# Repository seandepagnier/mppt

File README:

MPPT charge controller for maximum power

- free software and hardware design.  Can be adapted to other requirements.
- all ceramic capacitors.
- buck/boost design allow either higher or lower voltage of battery vs panel.
- components rated for up to 48 volt system (60 volt mosfets)
- voltage and current monitoring on both input and output.
- high-efficiency regulators to power the 3.3v logic as well as the 10v needed for gate drive.

This project uses the stm32duino environment.

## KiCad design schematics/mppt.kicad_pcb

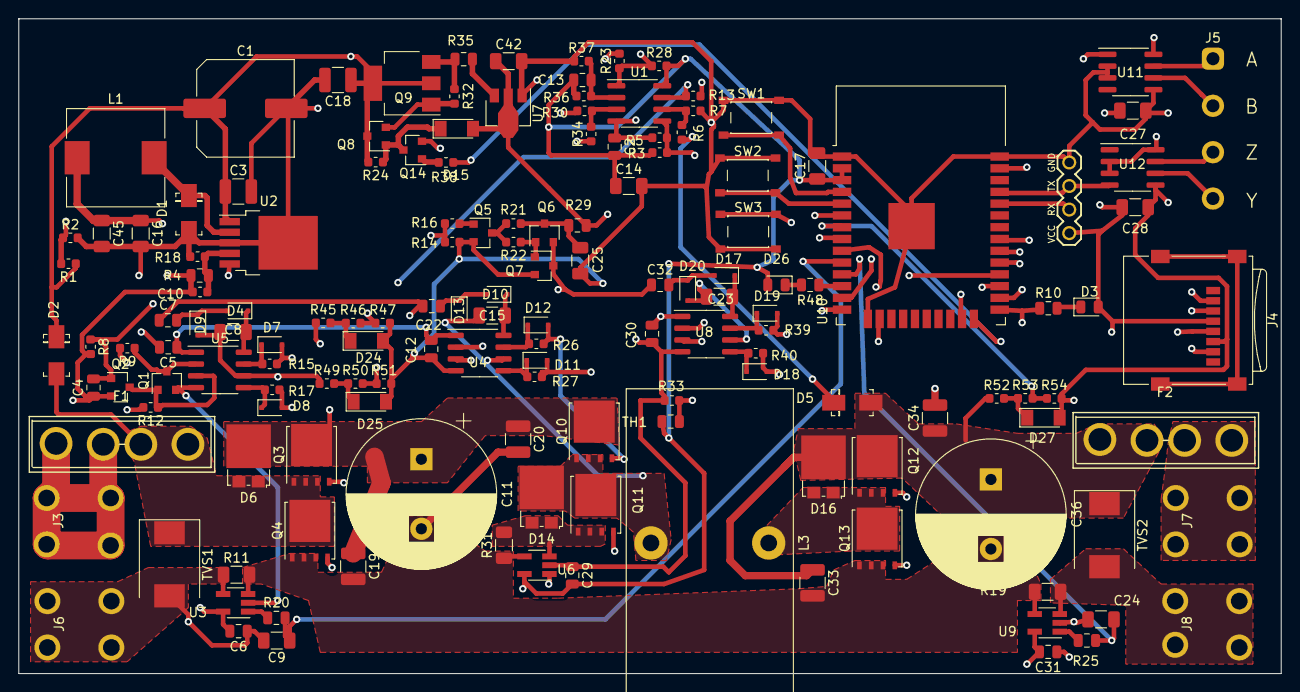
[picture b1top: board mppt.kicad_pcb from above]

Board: 4 copper layers, 136.1 x 70.6 mm, 152 parts (0 on the bottom side), 89 nets.

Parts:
C1: 33uF 100v; C_Elec_10x10.2
C2, C6, C7, C13, C22, C32: 100nF; C_0805_2012Metric
C3, C18: 4.7uF; C_1210_3225Metric
C4, C5, C12, C30: 10uF; C_0805_2012Metric
C8, C9, C15, C23, C24, C27, C28, C42: 1uF; C_1206_3216Metric
C10: 33nF; C_0603_1608Metric
C11, C36: 470uF; CP_Radial_D16.0mm_P7.50mm
C14, C16, C17, C25, C45: 10uF; C_1206_3216Metric
C19, C20, C33, C34: 4.7uF 100v; C_1210_3225Metric
C29, C31: 1uF; C_0805_2012Metric
D1, D2, D5: D; DO-214AC
D3: GREEN; LED_0805_2012Metric
D4, D7, D8, D9, D10, D11, D12, D13, D17, D18, D19, D20: D; D_SOD-323F
D6, D14, D16: D_Schottky_AAK; TO-277A
D15, D24, D25, D27: 5.6v; D_MiniMELF
D26: YELLOW; LED_0805_2012Metric
F1, F2: FUSE; BladeFuse-CarType
J2: UART; uart
J3: IN+; screw_terminal
J4: Micro_SD_Card; microSD_HC_Wuerth_693072010801
J5: Conn_01x04; rs422connector
J6: IN-; screw_terminal
J7: OUT+; screw_terminal
J8: OUT-; screw_terminal
L1: 100uH; L_10.4x10.4_H4.8
L3: 100uH; L_Toroid_Vertical_L33.0mm_W17.8mm_P12.70mm_Pulse_KM-5
Q1: Q_NMOS_GDS; SOT-23
Q2: Q_PMOS_GSD; SOT-23
Q3, Q4, Q10, Q11, Q12, Q13: Q_NMOS_GDS; TDSON-8-1
Q5, Q6, Q8, Q14: Q_NPN_BEC; SOT-23
Q7: Q_PNP_BCE; SOT-23
Q9: BCP56; SOT-223-3_TabPin2
R1: 20k; R_0603_1608Metric
R2, R3, R5, R14, R16, R18, R21, R22, R28, R33, R37, R46, R47, R50, R51, R53, R54: 10k; R_0603_1608Metric
R4: 120k; R_0805_2012Metric
R6: 47k; R_0603_1608Metric
R7, R32, R34: 1k; R_0603_1608Metric
R8, R9, R12, R23: 200k; R_0603_1608Metric
R10, R20, R25, R48: 510; R_0805_2012Metric
R11, R19, R31: .001; R_1206_3216Metric
R13, R24, R30, R36, R38: 100k; R_0603_1608Metric
R15, R17, R26, R27, R39, R40: 33; R_0603_1608Metric
R29, R35: 10; R_0805_2012Metric
R45, R49, R52: 333k; R_0603_1608Metric
SW1: page; SW_SPST_PTS810
SW2: menu; SW_SPST_PTS810
SW3: boot; SW_SPST_PTS810
TH1: Thermistor_NTC; R_0805_2012Metric
TVS1, TVS2: TVS; D_SMC
U1: LM393; SOIC-8_3.9x4.9mm_P1.27mm
U2: APE1707H-33-HF; TO-252-5_TabPin3
U3, U6, U9: INA180; SOT-23-5_HandSoldering
U4, U5, U8: lm5109; SO-8_3.9x4.9mm_P1.27mm
U7: AMS1117-5.0; SOT-89-3
U10: ESP32-WROOM-32D; ESP32-WROOM-32
U11, U12: ST485EBDR; SOIC-8_3.9x4.9mm_P1.27mm

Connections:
+3V3: C2.2, C4.1, C6.2, C10.1, C13.2, C14.1, C16.1, C17.1, C27.1, C28.1, C29.2, C31.2, C45.1, D3.2, D26.2, J2.1, J4.4, L1.1, Q2.2, R3.1, R4.1, R8.2, R28.2, R36.1, TH1.1, U1.8, U3.5, U6.5, U9.5, U10.2, U10.3, U11.8, U12.2, U12.3, U12.8
+12V: C5.1, C12.1, C30.1, C42.1, D15.2, R29.1, U4.1, U5.1, U7.2, U8.1
BOOST_H: U8.2, U10.16
BOOST_L: U8.3, U10.14
BUCK_H: U4.2, U10.23
BUCK_L: R23.2, U4.3, U10.13
CHARGE_PUMP: R14.1, R16.2, U10.26
GND: C1.2, C2.1, C3.2, C5.2, C6.1, C9.2, C12.2, C14.2, C16.2, C17.2, C18.2, C24.2, C25.1, C27.2, C28.2, C29.1, C30.2, C31.1, C42.2, C45.2, D1.2, D24.2, D25.2, D27.2, J2.4, J4.6, J6.1, Q1.2, Q5.2, Q7.2, Q14.2, R2.2, R5.2, R7.2, R11.1, R14.2, R18.2, R33.2, R37.1, R47.2, R51.2, R54.2, SW1.1, SW2.1, SW3.2, TVS1.2, U1.4, U2.3, U3.2, U3.4, U4.4, U5.4, U6.2, U7.1, U8.4, U9.2, U10.1, U10.15, U10.38, U10.39, U11.2, U11.3, U11.5, U12.5
HC: C9.1, R20.2, U10.10
HV: R46.2, R47.1, U10.6
IV: R50.2, R51.1, U10.9
LC: C24.1, R25.2, U10.11
LV: R53.2, R54.1, U10.7
unnamed: C1.1, C3.1, C18.1, D2.1, D5.1, Q8.3, Q9.2, R1.1, R6.1, R24.2, U2.1
unnamed: C4.2, Q2.1, R8.1, R13.1, U1.7
unnamed: C7.2, D4.2, D9.1
unnamed: C8.2, D4.1, U5.8
unnamed: C10.2, R4.2, R18.1, U2.4
unnamed: C11.2, C19.2, C20.2, C33.2, C34.2, C36.2, Q4.1, Q13.1, R11.2, R19.2, R31.1, U3.3, U6.4, U9.4
unnamed: C13.1, R36.2, R37.2, U1.2
unnamed: C15.1, D13.2, D14.3, L3.2, Q10.1, Q11.3, U4.6
unnamed: C15.2, D10.1, U4.8
unnamed: C7.1, C22.1, C32.1, Q6.2, Q7.3
unnamed: C22.2, D10.2, D13.1
unnamed: C23.1, D16.1, D16.2, D20.2, L3.1, Q12.1, Q13.3, U8.6
unnamed: C23.2, D17.1, U8.8
unnamed: C25.2, Q6.3, R21.1, R29.2
unnamed: C32.2, D17.2, D20.1
unnamed: D1.1, L1.2, U2.2
unnamed: D3.1, R10.2
unnamed: D7.1, R15.2, U5.7
unnamed: D7.2, Q3.2, R15.1
unnamed: D8.1, R17.2, U5.5
unnamed: D8.2, Q4.2, R17.1
unnamed: D11.1, R27.2, U4.5
unnamed: D11.2, Q11.2, R27.1
unnamed: D12.1, R26.2, U4.7
unnamed: D12.2, Q10.2, R26.1
unnamed: D14.1, D14.2, Q11.1, R31.2, U6.3
unnamed: D15.1, Q8.1, Q14.3, R24.1
unnamed: D18.1, R40.2, U8.5
unnamed: D18.2, Q13.2, R40.1
unnamed: D19.1, R39.2, U8.7
unnamed: D19.2, Q12.2, R39.1
unnamed: D24.1, R45.2, R46.1
unnamed: D25.1, R49.2, R50.1
unnamed: D26.1, R48.2
unnamed: D27.1, R52.2, R53.1
unnamed: F1.1, J3.1
unnamed: F2.2, J7.1
unnamed: J4.2, U10.29
unnamed: J4.3, U10.37
unnamed: J4.5, U10.30
unnamed: J4.7, U10.31
unnamed: J5.1, U11.7
unnamed: J5.2, U11.6
unnamed: J5.3, U12.7
unnamed: J5.4, U12.6
unnamed: J8.1, R19.1, TVS2.2, U9.3
unnamed: Q1.1, Q2.3, R12.1, U5.3
unnamed: Q1.3, R9.1, U5.2
unnamed: Q5.1, R16.1
unnamed: Q5.3, R21.2, R22.2
unnamed: Q6.1, Q7.1, R22.1
unnamed: Q8.2, Q9.1, R32.1
unnamed: Q9.3, R32.2, R35.2
unnamed: Q14.1, R38.1
unnamed: R1.2, R2.1, U2.5
unnamed: R6.2, R7.1, U1.6
unnamed: R10.1, SW3.1, U10.25
unnamed: R3.2, R5.1, R13.2, U1.5
unnamed: R20.1, U3.1
unnamed: R23.1, R28.1, R30.2, U1.1
unnamed: R25.1, U9.1
unnamed: R30.1, R34.2, U1.3
unnamed: R34.1, U6.1
unnamed: R35.1, U7.3
unnamed: R48.1, U10.12
unnamed: SW1.2, U10.4
unnamed: SW2.2, U10.5
PWRDWN: R38.2, U10.24
PWR_H: R9.2, U10.28
PWR_L: R12.2, U10.27
RX: J2.2, U10.34, U11.1
TEMP: R33.1, TH1.2, U10.8
TX: J2.3, U10.35, U12.4
VCC: C33.1, C34.1, C36.1, D5.2, D16.3, F2.1, Q12.3, R52.1, TVS2.1
VDD: C11.1, C19.1, C20.1, D6.3, Q3.3, Q10.3, R45.1
VEE: C8.1, D2.2, D6.1, D6.2, D9.2, F1.2, Q3.1, Q4.3, R49.1, TVS1.1, U5.6

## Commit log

2020-08-29 add mppt sketch
2020-08-29 add kicad schematics
2020-08-30 add option to set backlight on and off for buttons
2020-09-01 improve startup, allow set frequency from buttons
2020-09-02 improve startup
2023-02-12 update schematic
2023-03-09 improve schmatics
2023-03-09 update sketch
